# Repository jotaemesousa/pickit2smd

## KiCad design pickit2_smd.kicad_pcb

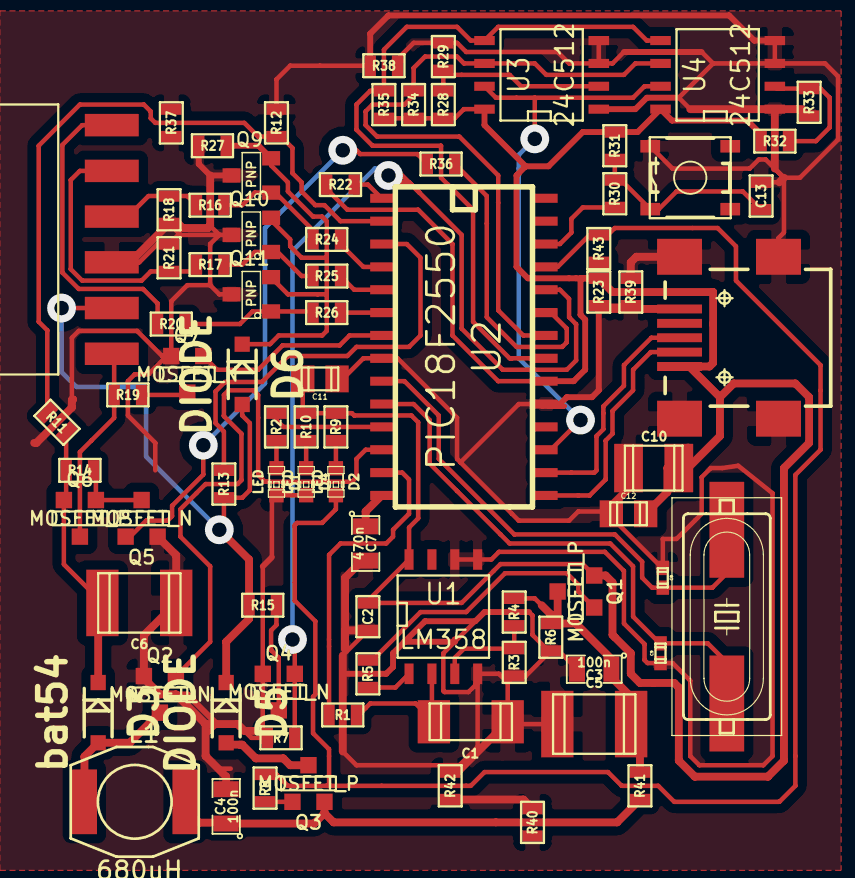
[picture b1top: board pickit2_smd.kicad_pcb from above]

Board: 2 copper layers, 81 parts (0 on the bottom side), 52 nets.

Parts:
C1: 100n; c_1808
C2, C13: 100n; SM0603
C3, C4: 100n; SM0805
C5: 10u; c_1812
C6: CAPAPOL; c_1812
C7: 470n; SM0805
C8, C9: 22p; c_0402
C10: 10u; c_1210
C11, C12: 100n; c_0805
CON1: USB-MINI-B; SparkFun-USB-MINIB
D1, D2, D4: LED; LED-0603
D3: bat54; SOD123_mod
D5, D6: DIODE; SOD123_mod
L1: 680uH; inductor_SDE6603
P1: CONN_6; SparkFun-1X06-SMD-FEMALE-V2
Q1, Q3, Q6: MOSFET_P; SOT23GDS
Q2, Q4, Q5, Q7: MOSFET_N; SOT23GDS
Q8: 20MHz; SparkFun-HC49UP
Q9, Q10, Q11: PNP; SOT23
R1, R3, R4, R6, R7, R14, R22, R31: 10k; SM0603
R2, R9, R10: 470; SM0603
R5, R19: 100; SM0603
R8, R12, R23: 2k7; SM0603
R11, R13, R18, R21: 4k7; SM0603
R15: 1k; SM0603
R16, R17, R20, R24, R25, R26, R30: 33; SM0603
R27: 820; SM0603
R28, R29, R32, R33, R34, R35: R; SM0603
R36, R37, R38, R39, R40, R41, R42: 0; SM0603
R43: 10K; SM0603
SW1: SW_PUSH_SMALL; SparkFun-TACTILE_SWITCH_SMD-2
U1: LM358; SO8N
U2: PIC18F2550; SO28
U3, U4: 24C512; SO8N

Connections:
+5V: C2.1, C10.1, C11.1, C12.1, CON1.1, Q1.S, R9.2, R10.2, R22.1, R23.1, R28.1, R31.1, R32.1, R34.1, R35.1, R43.2, U1.8, U2.20, U3.8, U4.8
/D+: CON1.3, U2.16
/D-: CON1.2, U2.15
/RA0: R11.2, R12.1, U2.2
/RA1: R13.2, U2.3
/RA2: R24.1, U2.4
/RA3: R25.1, U2.5
/RA4: R26.1, U2.6
/RA5: Q7.G, U2.7
/RB0: R35.2, U2.21, U3.5, U4.5
/RB1: R34.2, U2.22, U3.6, U4.6
/RB2: Q5.G, R36.1, R36.2, U2.23
/RB3: Q4.G, R7.1, U2.24
/RB4: D2.2, R8.2, R43.1, U2.25
/RB5: R30.1, U2.26
/RC0: R2.1, U2.11
/RC1: Q2.G, U2.12
/RC2: R1.1, U2.13
/RC6: U2.17, U3.7, U4.7
/clamp: D6.2, Q9.2, Q10.2, Q11.2, R27.2
GND: C1.2, C2.2, C3.2, C4.2, C5.2, C6.2, C7.2, C8.2, C9.2, C10.2, C11.2, C12.2, C13.2, CON1.5, CON1.6, CON1.7, CON1.8, CON1.9, D1.2, D4.2, P1.3, Q2.S, Q4.S, Q5.S, Q7.S, Q9.3, Q10.3, Q11.3, R3.1, R6.2, R7.2, R12.2, R18.2, R21.2, R23.2, R27.1, R29.2, R33.2, R37.1, R37.2, R38.1, R38.2, R39.1, R39.2, R40.1, R40.2, R42.1, R42.2, SW1.2, U1.4, U1.5, U1.6, U2.8, U2.19, U3.1, U3.3, U3.4, U4.1, U4.3, U4.4
unnamed: C1.1, R1.2, U1.2
unnamed: Q3.G, R8.1
unnamed: Q4.D, R15.1
unnamed: R3.2, R4.1, U1.3
unnamed: C13.1, R30.2, R31.2, SW1.1
unnamed: R28.2, R29.1, U3.2
unnamed: R32.2, R33.1, U4.2
unnamed: P1.6, R20.2
unnamed: Q10.1, R17.1, R25.2
unnamed: Q9.1, R16.1, R24.2
unnamed: C7.1, U2.14
unnamed: C4.1, L1.2, Q3.S, R41.2
unnamed: Q11.1, R20.1, R26.2
unnamed: Q5.D, Q6.G, R14.2
unnamed: D3.1, L1.1, Q2.D
unnamed: P1.1, Q6.D, R19.1
unnamed: P1.5, R17.2, R21.1
unnamed: P1.4, R16.2, R18.1
unnamed: D5.2, D6.1, P1.2, R13.1, R15.2
unnamed: C9.1, Q8.2, U2.10
unnamed: C8.1, Q8.1, U2.9
unnamed: D5.1, Q3.D
unnamed: C6.1, D3.2, Q6.S, R11.1, R14.1
unnamed: Q1.G, R5.1
unnamed: R5.2, U1.1
unnamed: D1.1, R2.2
unnamed: D2.1, R9.1
unnamed: D4.1, R10.1
unnamed: C3.1, C5.1, Q1.D, R4.2, R6.1, R41.1
unnamed: R22.2, U2.1
unnamed: Q7.D, R19.2

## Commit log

2014-02-01 initial
2014-03-06 footprint certo pic
2014-03-08 versao modificada, PCB 50%
2014-03-10 placa feita, falta a bobina e alargar pistas
2014-03-11 placa feita
2014-03-18 feito, shunt
